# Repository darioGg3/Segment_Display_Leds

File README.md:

# Segment_Display_Leds

PCB Display de 7 segmentos y 4 digitos hecho con LEDs SMD.

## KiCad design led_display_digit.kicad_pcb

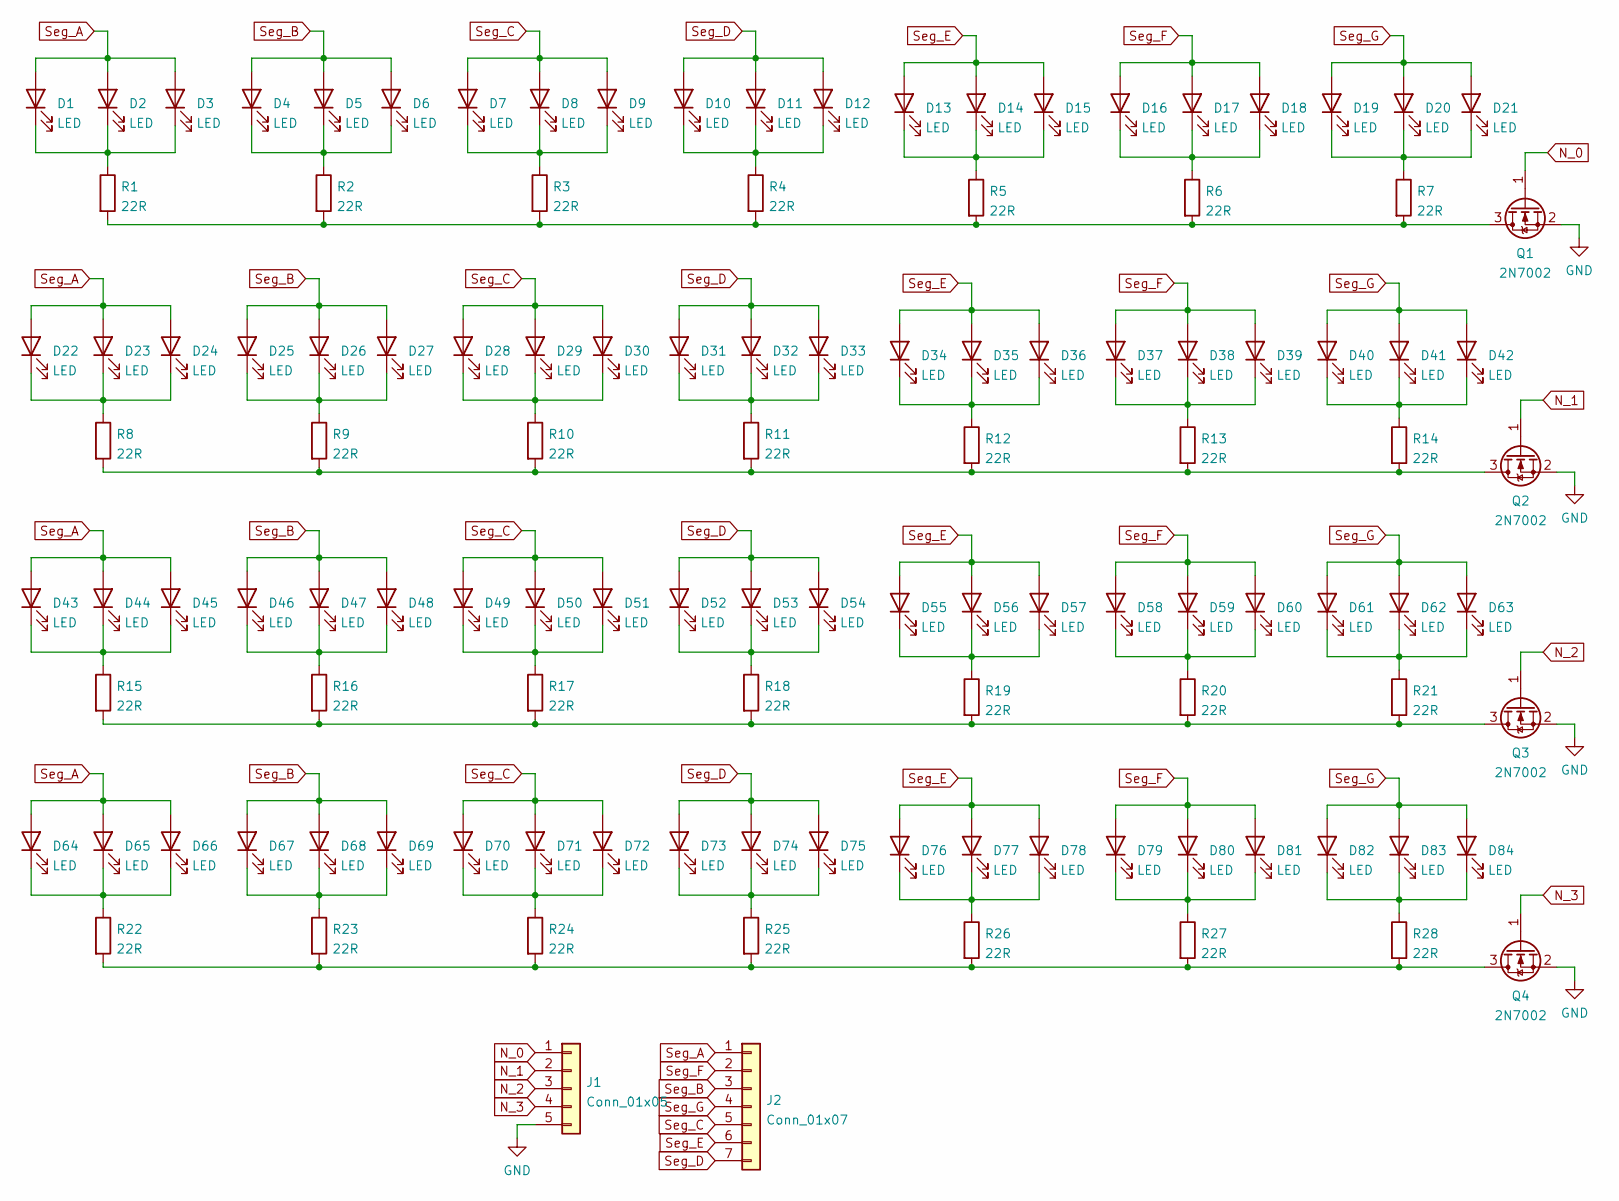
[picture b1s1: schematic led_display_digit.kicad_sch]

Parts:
D1, D2, D3, D4, D5, D6, D7, D8, D9, D10, D11, D12, D13, D14, D15, D16, D17, D18, D19, D20, D22, D23, D24, D25, D26, D27, D28, D29, D30, D31, D32, D33, D34, D35, D36, D37, D38, D39, D40, D41, D42, D43, D44, D45, D46, D47, D48, D49, D50, D51, D52, D53, D54, D55, D56, D57, D58, D59, D60, D61, D62, D63, D64, D65, D66, D67, D68, D69, D70, D71, D72, D73, D74, D75, D76, D77, D78, D79, D80, D81, D82, D83, D84: LED; LED_0402_1005Metric
D21: LED; R_0402_1005Metric
J1: Conn_01x05; PinHeader_1x05_P2.54mm_Vertical
J2: Conn_01x07; PinHeader_1x07_P2.54mm_Vertical
Q1, Q2, Q3, Q4: 2N7002; SOT-23
R1, R2, R3, R4, R5, R6, R7, R8, R9, R10, R11, R12, R13, R14, R15, R16, R17, R18, R19, R20, R21, R22, R23, R24, R25, R26, R27, R28: 22R; R_0402_1005Metric

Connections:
GND: J1.5, Q1.2 (S), Q2.2 (S), Q3.2 (S), Q4.2 (S); also elsewhere on the board
N_0: J1.1, Q1.1 (G)
N_1: J1.2, Q2.1 (G)
N_2: J1.3, Q3.1 (G)
N_3: J1.4, Q4.1 (G)
unnamed: D1.1 (K), D2.1 (K), D3.1 (K), R1.1
unnamed: D4.1 (K), D5.1 (K), D6.1 (K), R2.1
unnamed: D7.1 (K), D8.1 (K), D9.1 (K), R3.1
unnamed: D10.1 (K), D11.1 (K), D12.1 (K), R4.1
unnamed: D13.1 (K), D14.1 (K), D15.1 (K), R5.1
unnamed: D16.1 (K), D17.1 (K), D18.1 (K), R6.1
unnamed: D19.1 (K), D20.1 (K), D21.1 (K), R7.1
unnamed: D22.1 (K), D23.1 (K), D24.1 (K), R8.1
unnamed: D25.1 (K), D26.1 (K), D27.1 (K), R9.1
unnamed: D28.1 (K), D29.1 (K), D30.1 (K), R10.1
unnamed: D31.1 (K), D32.1 (K), D33.1 (K), R11.1
unnamed: D34.1 (K), D35.1 (K), D36.1 (K), R12.1
unnamed: D37.1 (K), D38.1 (K), D39.1 (K), R13.1
unnamed: D40.1 (K), D41.1 (K), D42.1 (K), R14.1
unnamed: D43.1 (K), D44.1 (K), D45.1 (K), R15.1
unnamed: D46.1 (K), D47.1 (K), D48.1 (K), R16.1
unnamed: D49.1 (K), D50.1 (K), D51.1 (K), R17.1
unnamed: D52.1 (K), D53.1 (K), D54.1 (K), R18.1
unnamed: D55.1 (K), D56.1 (K), D57.1 (K), R19.1
unnamed: D58.1 (K), D59.1 (K), D60.1 (K), R20.1
unnamed: D61.1 (K), D62.1 (K), D63.1 (K), R21.1
unnamed: D64.1 (K), D65.1 (K), D66.1 (K), R22.1
unnamed: D67.1 (K), D68.1 (K), D69.1 (K), R23.1
unnamed: D70.1 (K), D71.1 (K), D72.1 (K), R24.1
unnamed: D73.1 (K), D74.1 (K), D75.1 (K), R25.1
unnamed: D76.1 (K), D77.1 (K), D78.1 (K), R26.1
unnamed: D79.1 (K), D80.1 (K), D81.1 (K), R27.1
unnamed: D82.1 (K), D83.1 (K), D84.1 (K), R28.1
unnamed: Q1.3 (D), R1.2, R2.2, R3.2, R4.2, R5.2, R6.2, R7.2
unnamed: Q2.3 (D), R8.2, R9.2, R10.2, R11.2, R12.2, R13.2, R14.2
unnamed: Q3.3 (D), R15.2, R16.2, R17.2, R18.2, R19.2, R20.2, R21.2
unnamed: Q4.3 (D), R22.2, R23.2, R24.2, R25.2, R26.2, R27.2, R28.2
Seg_A: D1.2 (A), D2.2 (A), D3.2 (A), D22.2 (A), D23.2 (A), D24.2 (A), D43.2 (A), D44.2 (A), D45.2 (A), D64.2 (A), D65.2 (A), D66.2 (A), J2.1
Seg_B: D4.2 (A), D5.2 (A), D6.2 (A), D25.2 (A), D26.2 (A), D27.2 (A), D46.2 (A), D47.2 (A), D48.2 (A), D67.2 (A), D68.2 (A), D69.2 (A), J2.3
Seg_C: D7.2 (A), D8.2 (A), D9.2 (A), D28.2 (A), D29.2 (A), D30.2 (A), D49.2 (A), D50.2 (A), D51.2 (A), D70.2 (A), D71.2 (A), D72.2 (A), J2.5
Seg_D: D10.2 (A), D11.2 (A), D12.2 (A), D31.2 (A), D32.2 (A), D33.2 (A), D52.2 (A), D53.2 (A), D54.2 (A), D73.2 (A), D74.2 (A), D75.2 (A), J2.7
Seg_E: D13.2 (A), D14.2 (A), D15.2 (A), D34.2 (A), D35.2 (A), D36.2 (A), D55.2 (A), D56.2 (A), D57.2 (A), D76.2 (A), D77.2 (A), D78.2 (A), J2.6
Seg_F: D16.2 (A), D17.2 (A), D18.2 (A), D37.2 (A), D38.2 (A), D39.2 (A), D58.2 (A), D59.2 (A), D60.2 (A), D79.2 (A), D80.2 (A), D81.2 (A), J2.2
Seg_G: D19.2 (A), D20.2 (A), D21.2 (A), D40.2 (A), D41.2 (A), D42.2 (A), D61.2 (A), D62.2 (A), D63.2 (A), D82.2 (A), D83.2 (A), D84.2 (A), J2.4

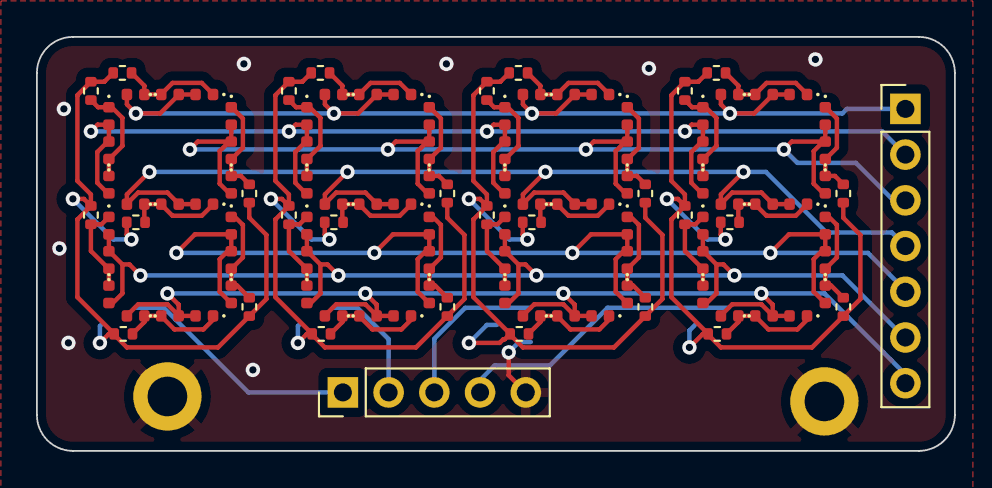
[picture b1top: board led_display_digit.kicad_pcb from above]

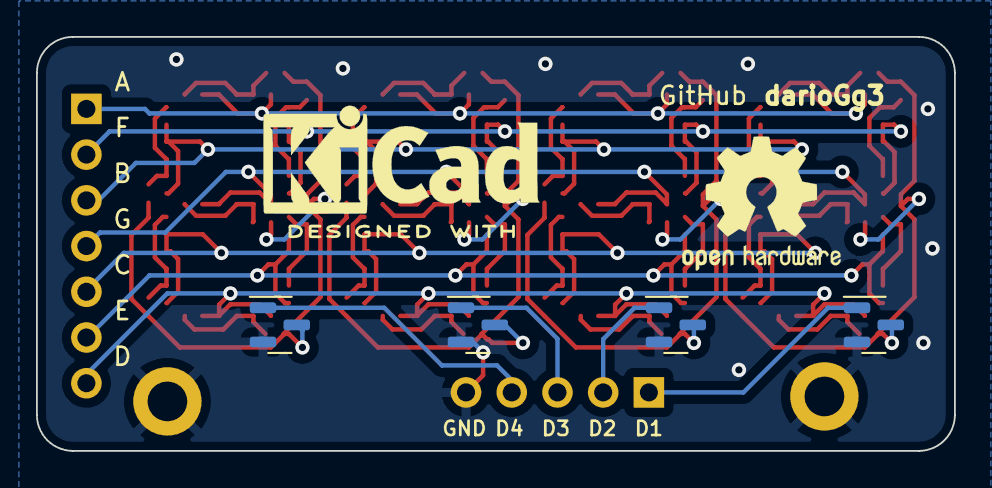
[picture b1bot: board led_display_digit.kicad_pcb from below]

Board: 2 copper layers, 51.0 x 23.0 mm, 120 parts (4 on the bottom side), 44 nets.

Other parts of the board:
H1, H2: MHole; MountingHole_2.2mm_M2_DIN965_Pad

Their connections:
GND: H1.1, H2.1; also elsewhere on the board

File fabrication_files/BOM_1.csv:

"Id","Designator","Footprint","Quantity","Comment","Supplier and ref",
1,"D6,D3,D81,D73,D7,D16,D17,D18,D58,D66,D46,D38,D39,D25,D80,D8,D70,D29,D48,D21,D69,D51,D28,D62,D5,D14,D67,D83,D59,D61,D56,D34,D63,D42,D50,D31,D4,D1,D24,D76,D72,D54,D9,D20,D40,D84,D45,D53,D2,D11,D60,D52,D26,D30,D57,D35,D75,D10,D74,D27,D49,D12,D15,D65,D22,D37,D79,D44,D68,D82,D77,D19,D33,D13,D78,D71,D64,D23,D55,D47,D41,D36,D32,D43","LED_0402_1005Metric",84,"LED",,,
2,"R6,R25,R26,R19,R1,R9,R7,R12,R8,R28,R5,R13,R16,R2,R3,R24,R17,R18,R20,R22,R15,R14,R4,R10,R21,R23,R27,R11","R_0402_1005Metric",28,"22R",,,

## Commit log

2022-03-30 init commit
2022-04-25 little design changes
2022-04-25 Readme complete
